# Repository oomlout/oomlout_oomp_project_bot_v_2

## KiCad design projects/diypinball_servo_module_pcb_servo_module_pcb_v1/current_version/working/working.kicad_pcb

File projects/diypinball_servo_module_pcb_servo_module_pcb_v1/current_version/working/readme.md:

# servo_module_pcb
 
## summary 
* id: diypinball_servo_module_pcb_servo_module_pcb_v1
* user: diypinball
* name: servo_module_pcb
* board: servo_module_pcb_v1
* repo: https://github.com/diypinball/servo-module-pcb
* src_file_repo_kicad_pcb: servo-module-pcb-v1.kicad_pcb
* src_file_repo_kicad_pcb_link: https://github.com/diypinball/servo-module-pcb/tree/master/servo-module-pcb-v1.kicad_pcb

* src_file_repo_sch: 
* src_file_repo_sch_link: https://github.com/diypinball/servo-module-pcb/tree/master/
* full details link: https://github.com/oomlout/oomlout_oomp_project_bot_v_2/tree/main/projects/diypinball_servo_module_pcb_servo_module_pcb_v1/current_version/working

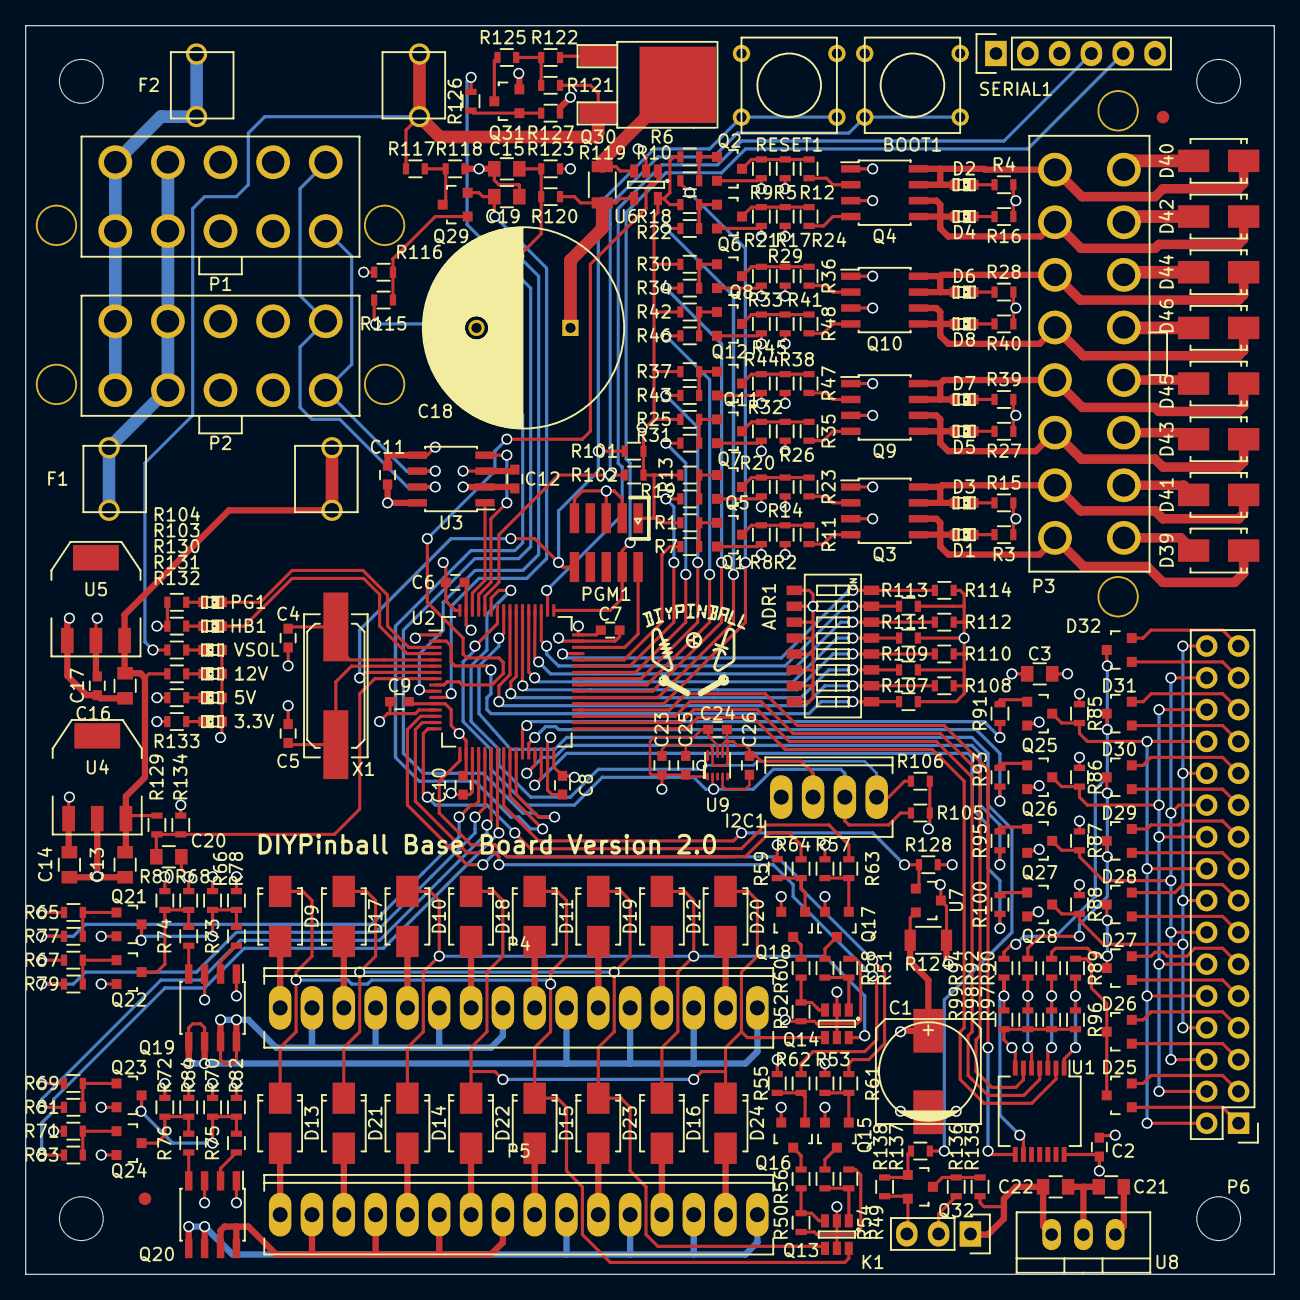
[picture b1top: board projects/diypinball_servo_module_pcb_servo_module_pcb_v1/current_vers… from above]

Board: 4 copper layers, 99.7 x 99.7 mm, 269 parts (0 on the bottom side), 202 nets.

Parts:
ADR1: DIPS_08; DIPSWITCH-SMT-08
BOOT1: BUTTON; SW_PUSH_SMALL
C1: 47u; c_elec_8x10
C2, C9, C10, C11, C12, C23, C24, C26: 100n; C_0603
C3, C13, C14, C15, C16, C19, C20, C21, C22: 10u; C_0805
C4, C5: 18p; C_0603
C6, C7, C8: 10n; C_0603
C17: 4.7u; C_0603
C18: 470u; C_Radial_D16_L25_P7.5
C25: 1u; C_0603
D1, D2, D3, D4, D5, D6, D7, D8, D35, D36, D37, D38: LED; LED-0603
D9, D10, D11, D12, D13, D14, D15, D16, D17, D18, D19, D20, D21, D22, D23, D24, D39, D40, D41, D42, D43, D44, D45, D46: S1M; Diode-SMA_Standard
D25, D26, D27, D28, D29, D30, D31, D32: BAT54C; SOT-23
F1, F2: FUSE; FC203-20MM
FIDUCIAL: VAL**; FIDUCIAL
FIDUCIAL#2: VAL**; FIDUCIAL
HB1: LED; LED-0603
I2C1: CONN_4; Socket_MOLEX-KK-RM2-54mm_Lock_4pin_straight
K1: CONN_3; Socket_Strip_Straight_1x03
P1, P2: PINBALL-CONNECTOR; PINBALL-CONNECTOR-V
P3: SOLENOID-CONNECTOR; SOLENOID-CONNECTOR-V
P4, P5: CONN_16; Socket_MOLEX-KK-RM2-54mm_Lock_16pin_straight
P6: HE10-32; Pin_Header_Straight_2x16
PG1: LED; LED-0603
PGM1: ARM-SWD-HEADER; pin_array_5x2_50mil_smd
Q1, Q2, Q5, Q6, Q7, Q8, Q11, Q12, Q15, Q16, Q17, Q18, Q21, Q22, Q23, Q24, Q25, Q26, Q27, Q28, Q31: BC846; SOT-23
Q3, Q4, Q9, Q10, Q19, Q20: DMN6040SSD; SOIC-8_3.9x4.9mm_Pitch1.27mm
Q13, Q14: DMP2240UDM; SOT-23-6
Q29, Q32: BSS138; SOT-23
Q30: FDD5614P; DPAK-2
R1, R6, R8, R9, R13, R18, R20, R21, R25, R30, R32, R33, R37, R42, R44, R45, R49, R50, R51, R52, R53, R55, R57, R59, R65, R67, R69, R71, R78, R80, R82, R84, R85, R86, R87, R88, R89, R90, R92, R94, R96, R97, R98, R99, R101, R102, R107, R108, R109, R110, R111, R112, R113, R114, R116, R121, R127, R138: 10K; R_0603
R2, R5, R7, R10, R14, R17, R19, R22, R26, R29, R31, R34, R38, R41, R43, R46, R54, R56, R58, R60, R61, R62, R63, R64, R66, R68, R70, R72, R77, R79, R81, R83, R91, R93, R95, R100, R103, R104, R115, R126, R132, R133, R135: 1K; R_0603
R3, R4, R15, R16, R27, R28, R39, R40, R131: 2.7K; R_0603
R11, R12, R23, R24, R35, R36, R47, R48, R73, R74, R75, R76, R122, R136, R137: 22; R_0603
R105, R106: 4.7K; R_0603
R117, R120: 95.3K 1%; R_0603
R118, R123, R128, R134: 5.1K 1%; R_0603
R119: .003; R_1206
R124: 0.075; R_1206
R125, R130: 27K; R_0603
R129: 20.5K 1%; R_0603
RESET1: BUTTON; SW_PUSH_SMALL
SERIAL1: FTDI_SERIAL; Socket_Strip_Straight_1x06
U1: 74LVC14; SSOP-14_5.3x6.2mm_Pitch0.65mm
U2: STM32F072R; LQFP-64_10x10mm_Pitch0.5mm
U3: MCP2562; SOIC-8_3.9x4.9mm_Pitch1.27mm
U4: MC78L05ACH; SOT-223
U5: AP1117IE33G; SOT-223
U6: ZXCT1086E5TA; SOT-23-5
U7: ZXCT1107SA-7; SOT-23
U8: LM7805CT; TO-220_Neutral123_Vertical
U9: MMA8653FC; DFN-10
X1: 8.000 MHz; Q_49U3HMS

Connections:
+3.3V: ADR1.1, ADR1.2, ADR1.3, ADR1.4, ADR1.5, ADR1.6, ADR1.7, ADR1.8, C2.1, C6.1, C7.1, C8.1, C9.1, C10.1, C11.1, C17.1, C23.1, C24.1, C25.1, I2C1.1, PGM1.1, R1.1, R6.1, R13.1, R18.1, R25.1, R30.1, R37.1, R42.1, R65.1, R67.1, R69.1, R71.1, R101.1, R102.1, R105.1, R106.1, R133.1, U1.14, U2.1, U2.13, U2.19, U2.32, U2.48, U2.64, U3.5, U5.2, U6.5, U9.1, U9.8
+5V: C12.1, C14.1, R132.1, U3.3, U4.1
+12V: C3.1, C13.1, C16.1, C21.1, F1.2, R2.1, R3.1, R4.1, R5.1, R14.1, R15.1, R16.1, R17.1, R26.1, R27.1, R28.1, R29.1, R38.1, R39.1, R40.1, R41.1, R85.1, R86.1, R87.1, R88.1, R124.2, R129.2, R131.1, U4.3, U5.3, U7.3, U8.1
/Accelerometer/SCL: I2C1.3, R105.2, U2.58, U9.2
/Accelerometer/SDA: I2C1.4, R106.2, U2.59, U9.10
/Control Logic/12V_SENSE: C20.1, R129.1, R134.1, U2.8
/Control Logic/ADDRESS0: ADR1.16, R114.1, U2.45
/Control Logic/ADDRESS1: ADR1.15, R113.1, U2.51
/Control Logic/ADDRESS2: ADR1.14, R112.1, U2.52
/Control Logic/ADDRESS3: ADR1.13, R111.1, U2.53
/Control Logic/ADDRESS4: ADR1.12, R110.1, U2.54
/Control Logic/ADDRESS5: ADR1.11, R109.1, U2.55
/Control Logic/ADDRESS6: ADR1.10, R108.1, U2.56
/Control Logic/ADDRESS7: ADR1.9, R107.1, U2.2
/Control Logic/BOOTLOADER: BOOT1.2, R102.2, U2.60
/Control Logic/CANH: P1.5, P2.5, U3.7
/Control Logic/CANL: P1.10, P2.10, U3.6
/Control Logic/CANRX: U2.61, U3.4
/Control Logic/CANTX: U2.62, U3.1
/Control Logic/HEARTBEAT: HB1.1, U2.4
/Control Logic/LAMP_COL0: R77.1, U2.20
/Control Logic/LAMP_COL1: R79.1, U2.21
/Control Logic/LAMP_COL2: R81.1, U2.22
/Control Logic/LAMP_COL3: R83.1, U2.23
/Control Logic/LAMP_ROW0: R61.1, U2.14
/Control Logic/LAMP_ROW1: R62.1, U2.15
/Control Logic/LAMP_ROW2: R63.1, U2.16
/Control Logic/LAMP_ROW3: R64.1, U2.17
/Control Logic/POWER_GOOD: PG1.1, U2.3
/Control Logic/RXD: SERIAL1.4, U2.50
/Control Logic/SOLENOID0: R7.1, U2.44
/Control Logic/SOLENOID1: R19.1, U2.43
/Control Logic/SOLENOID2: R31.1, U2.42
/Control Logic/SOLENOID3: R43.1, U2.41
/Control Logic/SOLENOID4: R46.1, U2.40
/Control Logic/SOLENOID5: R34.1, U2.39
/Control Logic/SOLENOID6: R22.1, U2.38
/Control Logic/SOLENOID7: R10.1, U2.37
/Control Logic/SWCLK: PGM1.4, SERIAL1.5, U2.49
/Control Logic/SWDIO: PGM1.2, U2.46
/Control Logic/VSOL_IN_SENSE: C15.1, Q29.2, U2.11
/Control Logic/VSOL_MEASURE_CONTROL: R115.2, U2.25
/Control Logic/VSOL_PRECHARGE_PWM: R126.2, U2.26
/Control Logic/VSOL_SENSE: C19.1, R120.2, R123.1, U2.10
/Control Logic/~RESET: PGM1.10, R101.2, RESET1.2, U2.7
/Lamp Driver/LAMP_12V: C1.1, Q13.2, Q13.5, Q14.2, Q14.5, R49.1, R50.1, R51.1, R52.1, R66.1, R68.1, R70.1, R72.1, R124.1, U7.2
/Power Supply/12V_IN: F1.1, P1.2, P1.7, P2.2, P2.7
/Power Supply/ILAMP_SENSE_OUT: R128.1, U2.24, U7.1
/Power Supply/ISOL_SENSE_OUT: U2.9, U6.1
/Power Supply/VSOL_IN: F2.1, P1.1, P1.6, P2.1, P2.6
/RGB LED Output/RGB_DATA: R137.2, U2.57
/Solenoid Driver/SOL_PWR: C18.1, D39.2, D40.2, D41.2, D42.2, D43.2, D44.2, D45.2, D46.2, P3.9, P3.10, P3.11, P3.12, P3.13, P3.14, P3.15, P3.16, R119.1, R120.1, U6.4
/Switch Matrix/COL0: R91.2, U2.27
/Switch Matrix/COL0_SWITCHED: P6.2, P6.10, P6.18, P6.26, Q25.3, R85.2
/Switch Matrix/COL1: R93.2, U2.28
/Switch Matrix/COL1_SWITCHED: P6.4, P6.12, P6.20, P6.28, Q26.3, R86.2
/Switch Matrix/COL2: R95.2, U2.29
/Switch Matrix/COL2_SWITCHED: P6.6, P6.14, P6.22, P6.30, Q27.3, R87.2
/Switch Matrix/COL3: R100.2, U2.30
/Switch Matrix/COL3_SWITCHED: P6.8, P6.16, P6.24, P6.32, Q28.3, R88.2
/Switch Matrix/ROW0: U1.2, U2.33
/Switch Matrix/ROW0_SWITCHED: D25.3, D26.3, R89.2
/Switch Matrix/ROW1: U1.4, U2.34
/Switch Matrix/ROW1_SWITCHED: D27.3, D28.3, R90.2
/Switch Matrix/ROW2: U1.6, U2.35
/Switch Matrix/ROW2_SWITCHED: D29.3, D30.3, R92.2
/Switch Matrix/ROW3: U1.8, U2.36
/Switch Matrix/ROW3_SWITCHED: D31.3, D32.3, R94.2
GND: BOOT1.1, C1.2, C2.2, C3.2, C4.2, C5.2, C6.2, C7.2, C8.2, C9.2, C10.2, C11.2, C12.2, C13.2, C14.2, C15.2, C16.2, C17.2, C18.2, C19.2, C20.2, C21.2, C22.2, C23.2, C24.2, C25.2, C26.2, D35.2, D36.2, D37.2, D38.2, I2C1.2, K1.3, P1.3, P1.4, P1.8, P1.9, P2.3, P2.4, P2.8, P2.9, PGM1.3, PGM1.5, PGM1.9, Q1.2, Q2.2, Q3.1, Q3.3, Q4.1, Q4.3, Q5.2, Q6.2, Q7.2, Q8.2, Q9.1, Q9.3, Q10.1, Q10.3, Q11.2, Q12.2, Q15.2, Q16.2, Q17.2, Q18.2, Q19.1, Q19.3, Q20.1, Q20.3, Q21.2, Q22.2, Q23.2, Q24.2, Q25.2, Q26.2, Q27.2, Q28.2, Q31.2, Q32.2, R8.2, R9.2, R20.2, R21.2, R32.2, R33.2, R44.2, R45.2, R53.1, R55.1, R57.1, R59.1, R78.2, R80.2, R82.2, R84.2, R96.2, R97.2, R98.2, R99.2, R103.2, R104.2, R107.2, R108.2, R109.2, R110.2, R111.2, R112.2, R113.2, R114.2, R116.2, R118.2, R123.2, R127.2, R128.2, R134.2, R138.2, RESET1.1, SERIAL1.1, U1.7, U2.12, U2.18, U2.31, U2.47, U2.63, U3.2, U3.8, U4.2, U5.1, U6.2, U8.2, U9.6, U9.7, U9.9
unnamed: C4.1, U2.5, X1.1
unnamed: C5.1, U2.6, X1.2
unnamed: C22.1, K1.1, R135.1, U8.3
unnamed: C26.1, U9.4
unnamed: D1.1, R3.2
unnamed: D1.2, D39.1, P3.1, Q3.5, Q3.6
unnamed: D2.1, R4.2
unnamed: D2.2, D40.1, P3.8, Q4.7, Q4.8
unnamed: D3.1, R15.2
unnamed: D3.2, D41.1, P3.2, Q3.7, Q3.8
unnamed: D4.1, R16.2
unnamed: D4.2, D42.1, P3.7, Q4.5, Q4.6
unnamed: D5.1, R27.2
unnamed: D6.1, R28.2
unnamed: D7.1, R39.2
unnamed: D8.1, R40.2
unnamed: D9.2, P4.1
unnamed: D10.1, D12.1, D14.1, D16.1, Q14.6
unnamed: D10.2, P4.5
unnamed: D9.1, D11.1, D13.1, D15.1, Q13.6
unnamed: D11.2, P4.9
unnamed: D12.2, P4.13
unnamed: D13.2, P5.1
unnamed: D14.2, P5.5
unnamed: D15.2, P5.9
unnamed: D16.2, P5.13
unnamed: D17.1, D19.1, D21.1, D23.1, Q13.4
unnamed: D17.2, P4.3
unnamed: D18.1, D20.1, D22.1, D24.1, Q14.4
unnamed: D18.2, P4.7
unnamed: D19.2, P4.11
unnamed: D20.2, P4.15
unnamed: D21.2, P5.3
unnamed: D22.2, P5.7
unnamed: D23.2, P5.11
unnamed: D24.2, P5.15
unnamed: D25.1, P6.1
unnamed: D25.2, P6.3
unnamed: D26.1, P6.5
unnamed: D26.2, P6.7
unnamed: D27.1, P6.9
unnamed: D27.2, P6.11
unnamed: D28.1, P6.13
unnamed: D28.2, P6.15
unnamed: D29.1, P6.17
unnamed: D29.2, P6.19
unnamed: D30.1, P6.21
unnamed: D30.2, P6.23
unnamed: D31.1, P6.25
unnamed: D31.2, P6.27
unnamed: D32.1, P6.29
unnamed: D32.2, P6.31
unnamed: D35.1, R130.2
unnamed: D36.1, R131.2
unnamed: D37.1, R132.2
unnamed: D38.1, R133.2
unnamed: D5.2, D43.1, P3.3, Q9.5, Q9.6
unnamed: D6.2, D44.1, P3.6, Q10.7, Q10.8
unnamed: D7.2, D45.1, P3.4, Q9.7, Q9.8
unnamed: D8.2, D46.1, P3.5, Q10.5, Q10.6
unnamed: HB1.2, R103.1
unnamed: K1.2, R136.1
unnamed: P4.2, P4.4, P4.6, P4.8, Q19.7, Q19.8
unnamed: P4.10, P4.12, P4.14, P4.16, Q19.5, Q19.6
unnamed: P5.2, P5.4, P5.6, P5.8, Q20.7, Q20.8
unnamed: P5.10, P5.12, P5.14, P5.16, Q20.5, Q20.6
unnamed: PG1.2, R104.1
unnamed: Q1.1, R1.2, R7.2
unnamed: Q1.3, R2.2, R8.1, R11.2
unnamed: Q2.1, R6.2, R10.2
unnamed: Q2.3, R5.2, R9.1, R12.1
unnamed: Q3.2, R23.1
unnamed: Q3.4, R11.1
unnamed: Q4.2, R12.2
unnamed: Q4.4, R24.2
unnamed: Q5.1, R13.2, R19.2
unnamed: Q5.3, R14.2, R20.1, R23.2
unnamed: Q6.1, R18.2, R22.2
unnamed: Q6.3, R17.2, R21.1, R24.1
unnamed: Q7.1, R25.2, R31.2
unnamed: Q7.3, R26.2, R32.1, R35.2
unnamed: Q8.1, R30.2, R34.2
unnamed: Q8.3, R29.2, R33.1, R36.1
unnamed: Q9.2, R47.1
unnamed: Q9.4, R35.1
unnamed: Q10.2, R36.2
unnamed: Q10.4, R48.2
unnamed: Q11.1, R37.2, R43.2
unnamed: Q11.3, R38.2, R44.1, R47.2
unnamed: Q12.1, R42.2, R46.2
unnamed: Q12.3, R41.2, R45.1, R48.1
unnamed: Q13.1, R49.2, R54.1
unnamed: Q13.3, R50.2, R56.1
unnamed: Q14.1, R51.2, R58.1
unnamed: Q14.3, R52.2, R60.1
unnamed: Q15.1, R53.2, R61.2
unnamed: Q15.3, R54.2
unnamed: Q16.1, R55.2, R62.2
unnamed: Q16.3, R56.2
unnamed: Q17.1, R57.2, R63.2
unnamed: Q17.3, R58.2
unnamed: Q18.1, R59.2, R64.2
unnamed: Q18.3, R60.2
unnamed: Q19.2, R73.1
unnamed: Q19.4, R74.2
unnamed: Q20.2, R75.2
unnamed: Q20.4, R76.2
unnamed: Q21.1, R65.2, R77.2
unnamed: Q21.3, R66.2, R73.2, R78.1
unnamed: Q22.1, R67.2, R79.2
unnamed: Q22.3, R68.2, R74.1, R80.1
unnamed: Q23.1, R69.2, R81.2
unnamed: Q23.3, R70.2, R75.1, R82.1
unnamed: Q24.1, R71.2, R83.2
unnamed: Q24.3, R72.2, R76.1, R84.1
unnamed: Q25.1, R91.1
unnamed: Q26.1, R93.1
unnamed: Q27.1, R95.1
unnamed: Q28.1, R100.1
unnamed: Q29.1, R115.1, R116.1
unnamed: Q29.3, R117.1, R118.1
unnamed: Q30.D, R119.2, U6.3
unnamed: Q30.G, R122.1
unnamed: Q31.1, R126.1, R127.1
unnamed: Q31.3, R125.2
unnamed: Q32.1, R137.1, R138.1
unnamed: Q32.3, R135.2, R136.2
unnamed: R89.1, R96.1, U1.1
unnamed: R90.1, R97.1, U1.3
unnamed: R92.1, R98.1, U1.5
unnamed: R94.1, R99.1, U1.9
unnamed: R121.2, R122.2, R125.1
VEE: F2.2, Q30.S, R117.2, R121.1, R130.1
